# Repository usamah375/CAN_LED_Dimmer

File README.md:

# CAN_LED_Dimmer

The files were created using Eagle v7.7

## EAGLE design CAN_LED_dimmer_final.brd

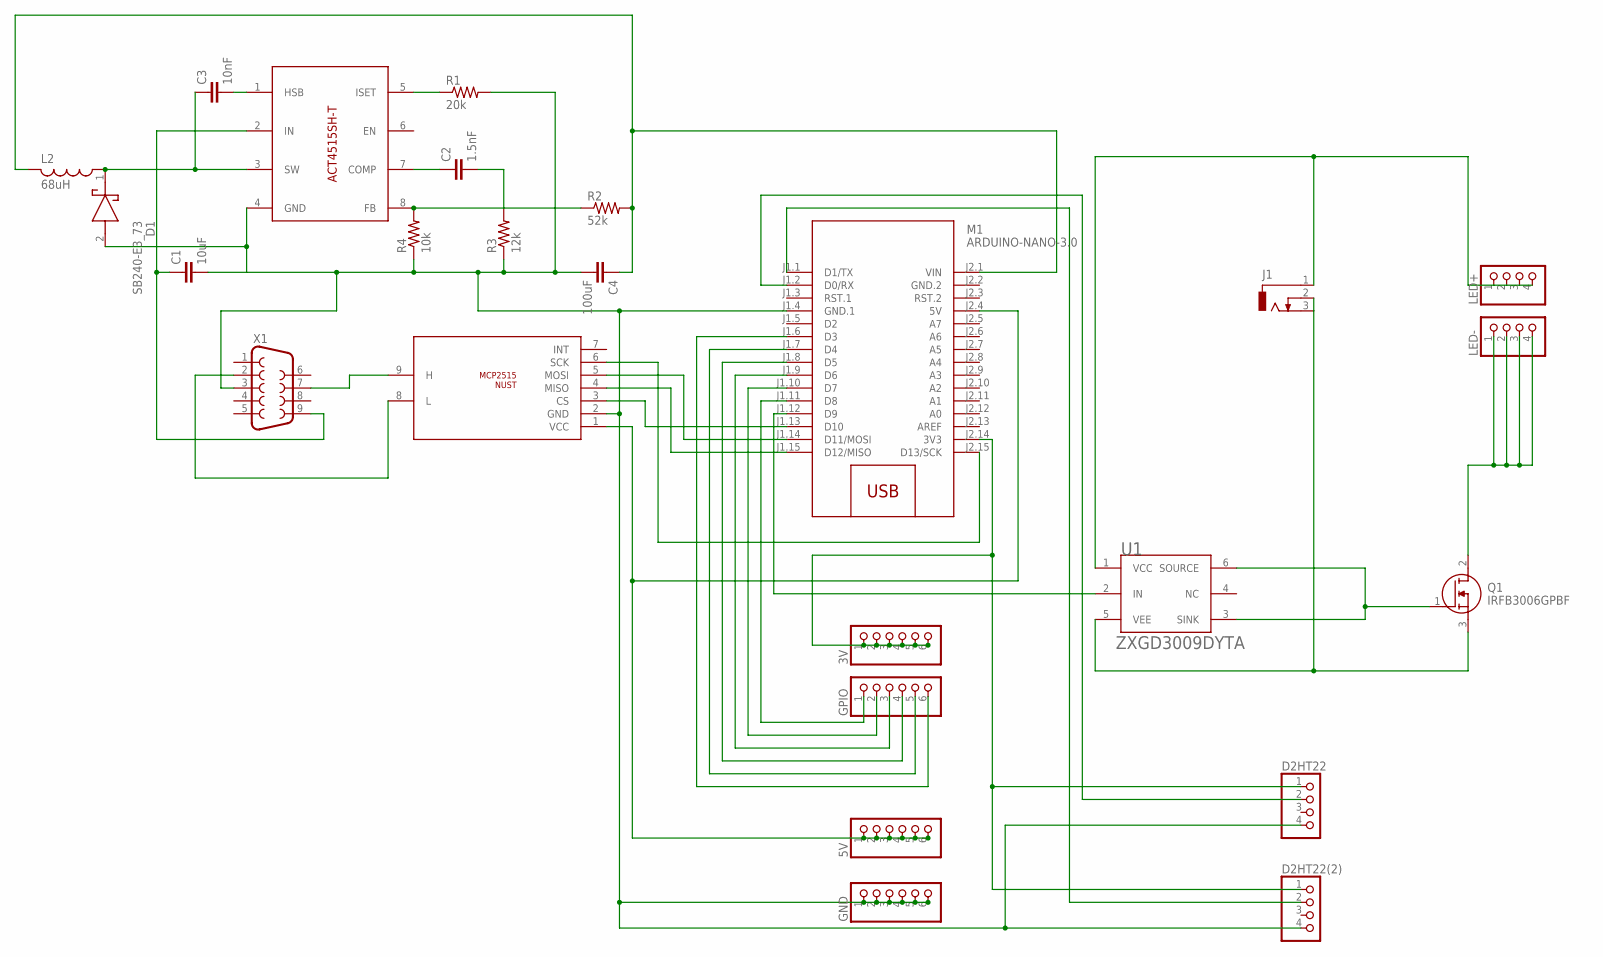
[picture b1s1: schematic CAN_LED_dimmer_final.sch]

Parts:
3V, 5V: PINHD-1X6; 1X06
C1: 10uF; C2.5-3
C2: 1.5nF; C2.5-3
C3: 10nF; C2.5-3
C4: 100uF; C2.5-3
D1: SB240-E3_73; DIOAD1910W70L670D310
D2HT22, D2HT22(2): PINHD-1X4; 1X04
GND: PINHD-1X6; 1X06
GPIO: PINHD-1X6; 1X06
J1: DCJ0303
L2: 68uH; 0204/7
LED+: PINHD-1X4; 1X04
LED-: PINHD-1X4; 1X04
M1: ARDUINO-NANO-3.0
Q1: IRFB3006GPBF; TO254P420X1016X1994-3P
R1: 20k; 0204/7
R2: 52k; 0204/7
R3: 12k; 0204/7
R4: 10k; 0204/7
U1: DIODES_ZXGD3009DYTADIODES_ZXGD3009DYTA_0_0; DIODES_ZXGD3009DYTA_0
U$1: MCP2515THROUGH_HOLE; MCP2515
U$2: ACT4515SH-T
X1: F09D

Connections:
GND.2: M1.J2.2 (GND.2)
unnamed: U$1.9 (H), X1.7
unnamed: U$1.8 (L), X1.2
unnamed: M1.J1.15 (D12/MISO), U$1.4 (MISO)
unnamed: M1.J1.14 (D11/MOSI), U$1.5 (MOSI)
unnamed: M1.J2.15 (D13/SCK), U$1.6 (SCK)
unnamed: M1.J1.13 (D10), U$1.3 (CS)
unnamed: 5V.1, 5V.2, 5V.3, 5V.4, 5V.5, 5V.6, M1.J2.4 (5V), U$1.1 (VCC)
unnamed: C1.2, C4.2, D1.2 (A), D2HT22.4, D2HT22(2).4, GND.1, GND.2, GND.3, GND.4, GND.5, GND.6, M1.J1.4 (GND.1), R1.2, R3.1, R4.1, U$1.2 (GND), U$2.4 (GND), X1.3
unnamed: C1.1, U$2.2 (IN), X1.9
unnamed: R1.1, U$2.5 (ISET)
unnamed: C2.2, R3.2
unnamed: C2.1, U$2.7 (COMP)
unnamed: C3.2, U$2.1 (HSB)
unnamed: R2.1, R4.2, U$2.8 (FB)
unnamed: C3.1, D1.1 (K), L2.1, U$2.3 (SW)
unnamed: C4.1, L2.2, M1.J2.1 (VIN), R2.2
unnamed: J1.2, J1.3, Q1.3 (S), U1.5 (VEE)
unnamed: M1.J1.12 (D9), U1.2 (IN)
unnamed: J1.1, LED+.1, LED+.2, LED+.3, LED+.4, U1.1 (VCC)
unnamed: LED-.1, LED-.4, Q1.2 (D)
unnamed: 3V.1, 3V.2, 3V.3, 3V.4, 3V.5, 3V.6, D2HT22.1, D2HT22(2).1, M1.J2.14 (3V3)
unnamed: GPIO.1, M1.J1.11 (D8)
unnamed: GPIO.2, M1.J1.10 (D7)
unnamed: GPIO.3, M1.J1.9 (D6)
unnamed: GPIO.4, M1.J1.8 (D5)
unnamed: GPIO.5, M1.J1.7 (D4)
unnamed: GPIO.6, M1.J1.6 (D3)
unnamed: D2HT22(2).2, M1.J1.1 (D1/TX)
unnamed: D2HT22.2, M1.J1.2 (D0/RX)
unnamed: Q1.1 (G), U1.3 (SINK), U1.6 (SOURCE)

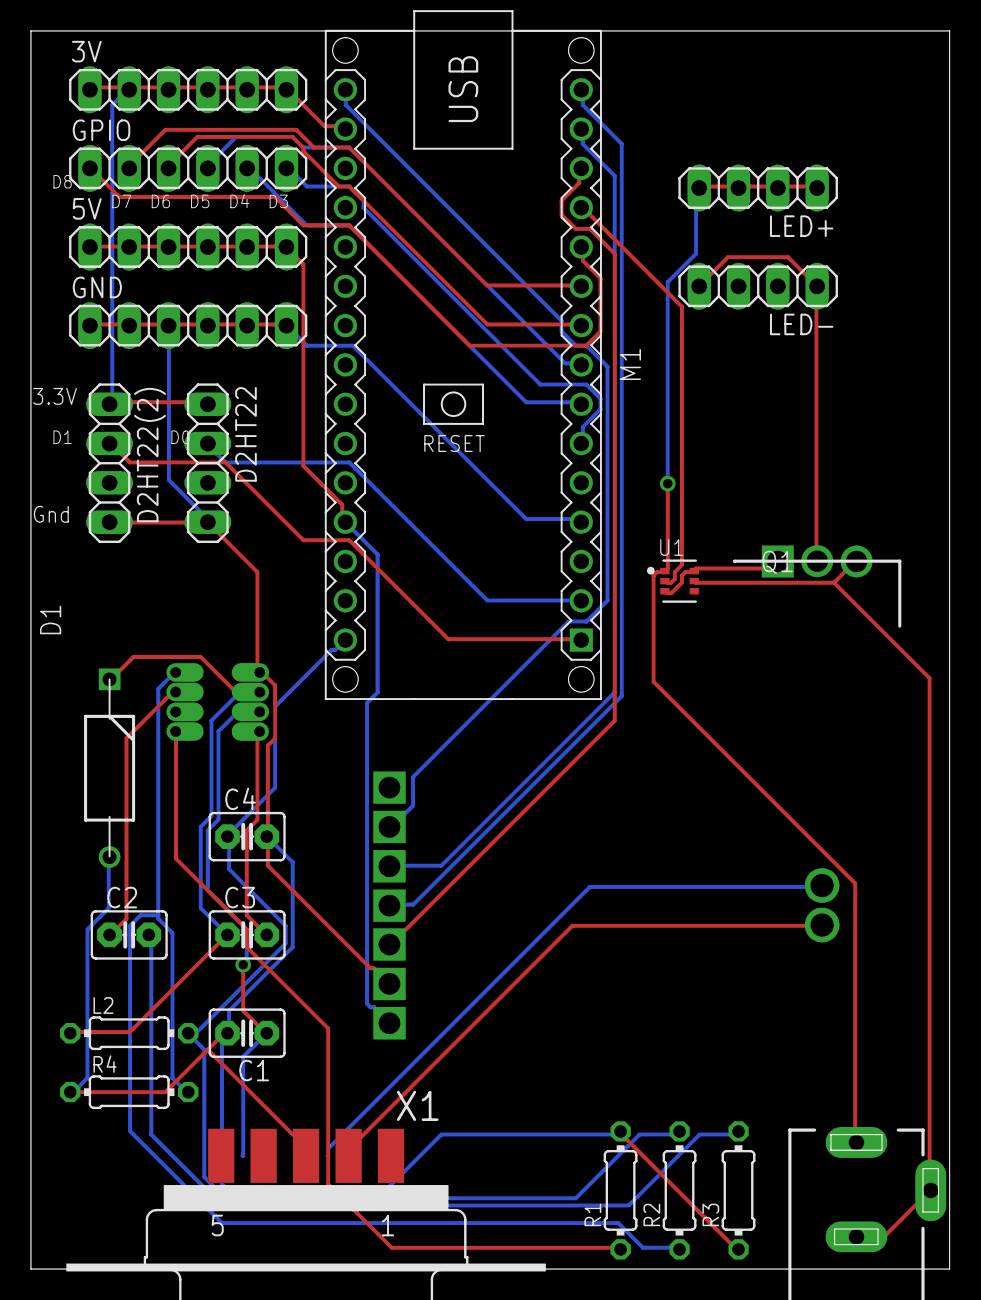
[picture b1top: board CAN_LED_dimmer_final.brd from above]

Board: 2 copper layers, 59.4 x 80.0 mm, 25 parts (0 on the bottom side), 30 nets.

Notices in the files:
parts and their libraries:
diy-modules: Released under the Creative Commons Attribution 4.0 International License: http://creativecommons.org/licenses/by/4.0
